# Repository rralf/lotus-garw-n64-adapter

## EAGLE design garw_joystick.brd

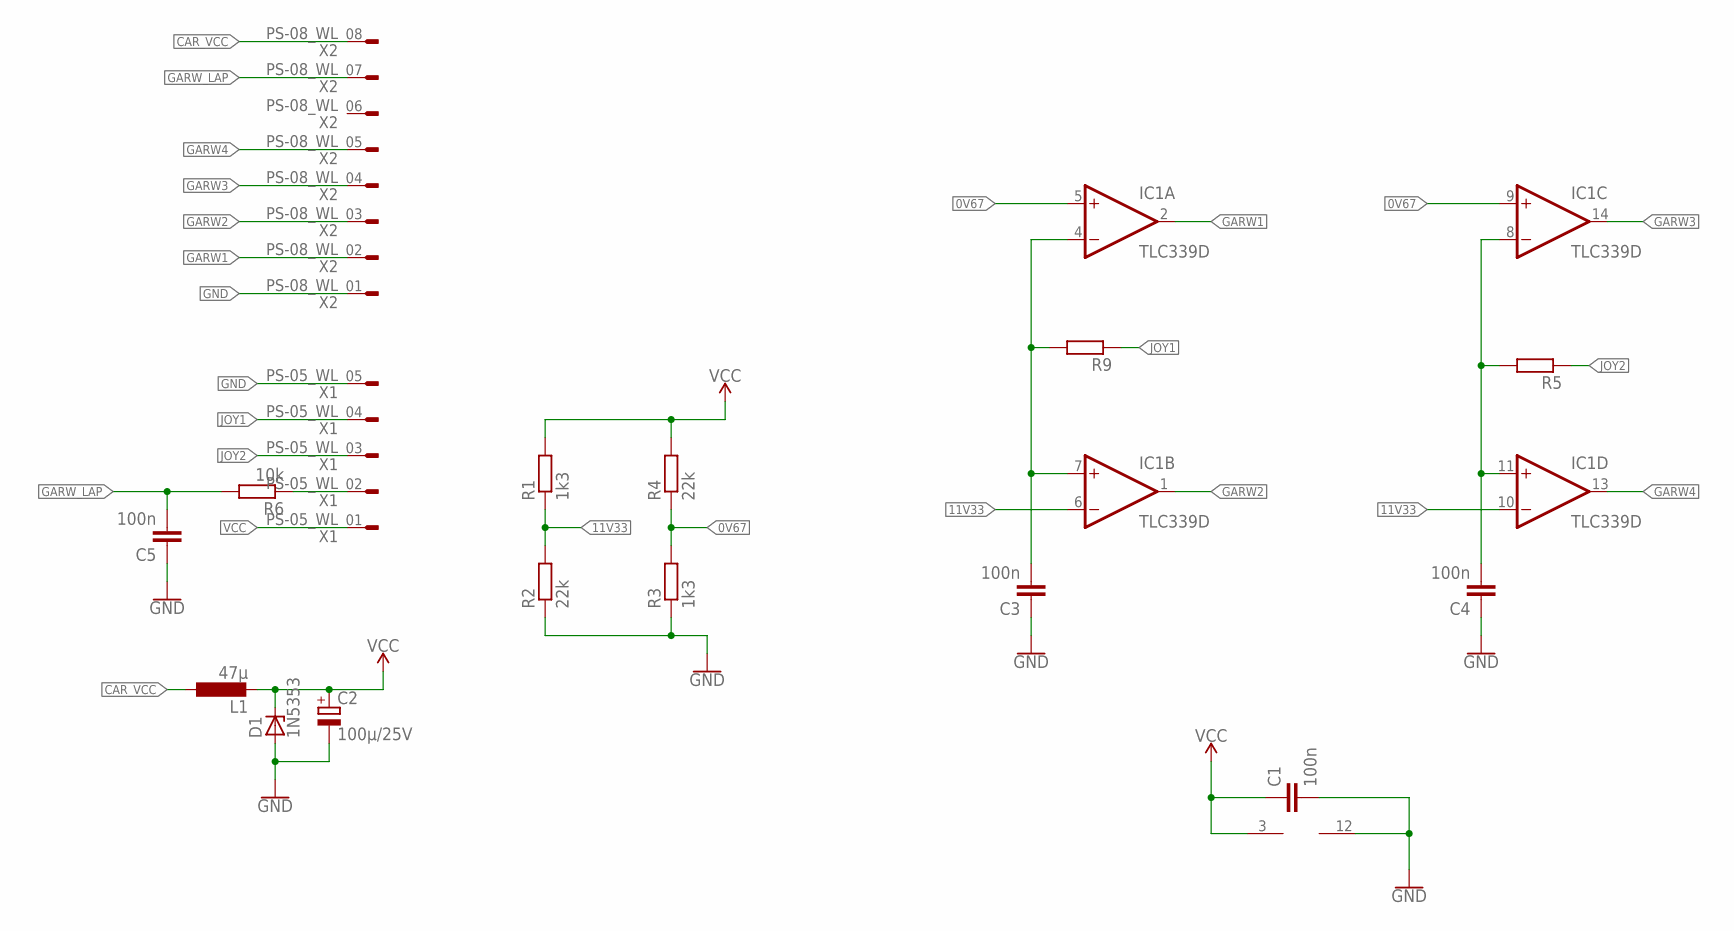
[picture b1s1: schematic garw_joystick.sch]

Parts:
C1, C3, C4, C5: 100n; C0805
C2: 100µ/25V; 153CLV-0605
D1: 1N5353; DO35Z10
IC1: TLC339D; SO14
L1: 47µ; 0204/7
R1, R3: 1k3; M0805
R2, R4: 22k; M0805
R5, R9: R-EU_M0805; M0805
R6: 10k; M0805
X1: PS-05_WL
X2: PS-08_WL

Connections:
0V67: IC1.5 (+IN), IC1.9 (+IN), R3.2, R4.1
11V33: IC1.6 (-IN), IC1.10 (-IN), R1.1, R2.2
CAR_VCC: L1.1, X2.08
GARW1: IC1.2 (OUT), X2.02
GARW2: IC1.1 (OUT), X2.03
GARW3: IC1.14 (OUT), X2.04
GARW4: IC1.13 (OUT), X2.05
GARW_LAP: C5.2, R6.2, X2.07
GND: C1.2, C2.-, C3.1, C4.1, C5.1, D1.A, IC1.12 (V-), R2.1, R3.1, X1.05, X2.01
JOY1: R9.1, X1.04
JOY2: R5.1, X1.03
unnamed: R6.1, X1.02
unnamed: C4.2, IC1.8 (-IN), IC1.11 (+IN), R5.2
unnamed: C3.2, IC1.4 (-IN), IC1.7 (+IN), R9.2
VCC: C1.1, C2.+, D1.C, IC1.3 (V+), L1.2, R1.2, R4.2, X1.01

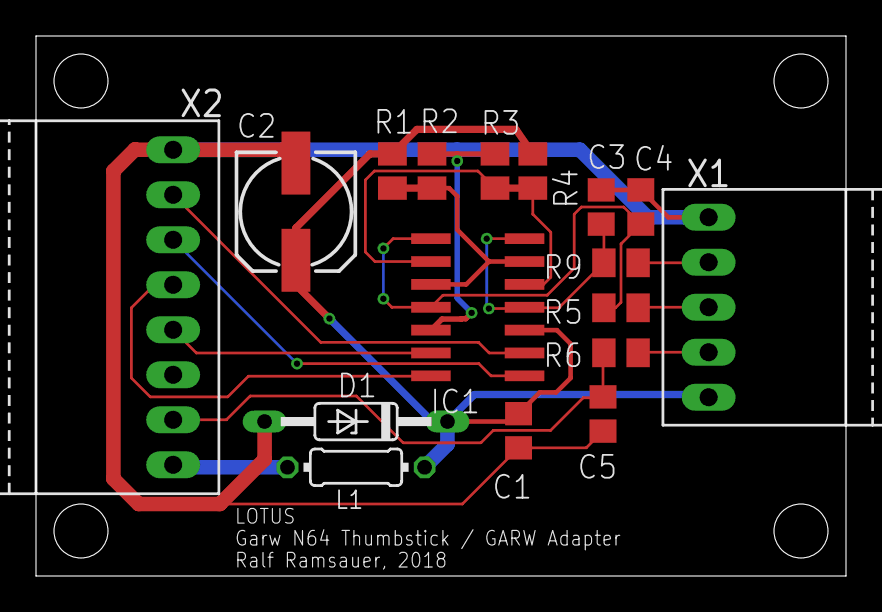
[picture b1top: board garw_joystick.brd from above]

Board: 2 copper layers, 45.0 x 30.0 mm, 17 parts (0 on the bottom side), 15 nets.

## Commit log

2018-12-26 Add images
2018-12-26 Add GPLv2 License
2018-12-26 Minot stylistic fixup
2018-12-27 Add .gitignore
2018-12-27 Improve board
2018-12-28 Add low pass filters
2019-01-12 Flip 0V6 and 11V3 net
    They were placed in the opposite way.

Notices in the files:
parts and their libraries:
SparkFun-Aesthetics: Licensing: Creative Commons ShareAlike 4.0 International - https://creativecommons.org/licenses/by-sa/4.0
